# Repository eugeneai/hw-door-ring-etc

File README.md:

# hw-door-ring-etc
Door ring and clock with mp3 and calendar ic on the base of arduino uno

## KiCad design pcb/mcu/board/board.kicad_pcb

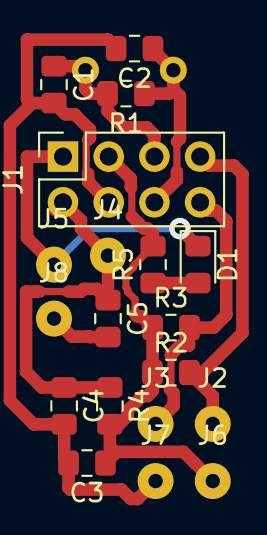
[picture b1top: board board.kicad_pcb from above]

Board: 2 copper layers, 20 parts (1 on the bottom side), 10 nets.

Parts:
C1, C2: 22p; C_0805_2012Metric_Pad1.15x1.40mm_HandSolder
C3, C4, C5: 100n; C_0805_2012Metric_Pad1.15x1.40mm_HandSolder
D1: LED; LED_0805_2012Metric_Pad1.15x1.40mm_HandSolder
J1: Conn_02x04_Odd_Even; PinSocket_2x04_P2.54mm_Vertical
J2: SCL; SolderWirePad_1x01_Drill0.8mm
J3: SDA; SolderWirePad_1x01_Drill0.8mm
J4: ~RST; SolderWirePad_1x01_Drill0.8mm
J5: PG4; SolderWirePad_1x01_Drill0.8mm
J6: VCC; SolderWirePad_1x01_Drill0.8mm
J7: GND; SolderWirePad_1x01_Drill0.8mm
J8: DTR; SolderWirePad_1x01_Drill0.8mm
R1: 1M; R_0805_2012Metric_Pad1.15x1.40mm_HandSolder
R2, R3: 10K; R_0805_2012Metric_Pad1.15x1.40mm_HandSolder
R4, R5: 1K; R_0805_2012Metric_Pad1.15x1.40mm_HandSolder
Y1: Crystal; Crystal_HC49-4H_Vertical

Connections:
GND: C1.2, C2.2, C3.2, C4.2, J1.4, J7.1
unnamed: C5.2, J8.1
unnamed: D1.2, R5.1
PG4: D1.1, J1.1, J5.1
SCL: J1.7, J2.1, R2.2
SDA: J1.8, J3.1, R3.2
VCC: C3.1, J1.3, J6.1, R2.1, R3.1, R4.2, R5.2
XTAL1: C2.1, J1.6, R1.1, Y1.2
XTAL2: C1.1, J1.5, R1.2, Y1.1
~RST: C4.1, C5.1, J1.2, J4.1, R4.1

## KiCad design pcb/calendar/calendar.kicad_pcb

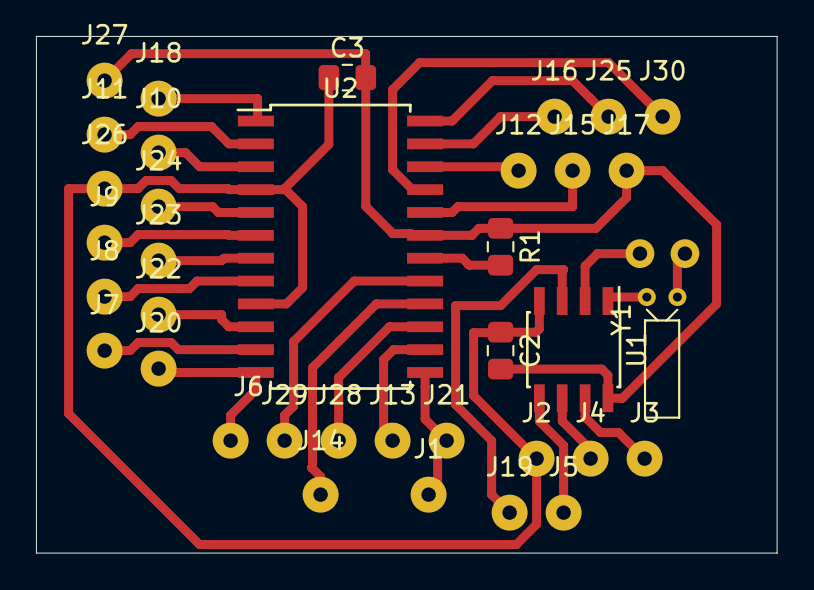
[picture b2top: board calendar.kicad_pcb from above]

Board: 4 copper layers, 41.1 x 28.7 mm, 37 parts (1 on the bottom side), 30 nets.

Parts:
C1: C; C_Disc_D3.0mm_W2.0mm_P2.50mm
C2, C3: 100n; C_0805_2012Metric_Pad1.15x1.40mm_HandSolder
J1, J2, J3, J4, J5, J6, J7, J8, J9, J10, J11, J12, J13, J14, J15, J16, J17, J18, J19, J20, J21, J22, J23, J24, J25, J26, J27, J28, J29, J30: J; SolderWirePad_1x01_Drill0.8mm
R1: 9K53; R_0805_2012Metric_Pad1.15x1.40mm_HandSolder
U1: PCF8563T; SOIC-8_3.9x4.9mm_P1.27mm
U2: MAX7219; SOIC-24W_7.5x15.4mm_P1.27mm
Y1: 32 768; Crystal_DS15_D1.5mm_L5.0mm_Horizontal

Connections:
+5V: C2.2, C3.2, J17.1, J27.1, R1.1, U1.8, U2.19
A: J13.1, U2.14
B: J14.1, U2.16
C: J15.1, U2.20
D: J16.1, U2.23
D0: J11.1, U2.2
D1: J7.1, U2.11
D2: J9.1, U2.6
D3: J23.1, U2.7
D4: J10.1, U2.3
D5: J22.1, U2.10
D6: J24.1, U2.5
D7: J8.1, U2.8
DIN: J18.1, U2.1
DOUT: J25.1, U2.24
DP: J12.1, U2.22
E: J30.1, U2.21
F: J28.1, U2.15
G: J29.1, U2.17
GND: C2.1, C3.1, J2.1, J26.1, U1.4, U2.4, U2.9
LOAD: J6.1, J20.1, U2.12
unnamed: C1.1, U1.2
unnamed: C1.2, Y1.2
unnamed: R1.2, U2.18
unnamed: U1.1, Y1.1
SCL: J4.1, U1.6
SCLK: J1.1, J21.1, U2.13
SDA: J5.1, U1.5
TCLK: J3.1, U1.7
T~INT: J19.1, U1.3

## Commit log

2019-04-06 Added code and doc
2019-04-06 Added ic docs.
2019-04-06 Added DFPlayer datasheet.
2019-04-07 Added some more ducs.
2019-04-07 Added PCB of clendar.
2019-04-09 Added 7-segment indicator theory.
2019-04-09 Show image in md.
2019-04-09 Another picture.
2019-04-09 Added new picture of pinout.
2019-04-16 Added more docs for mp3 player
2019-04-17 Moved pins around eliminating vias.
2019-04-18 New pcb
2019-04-18 Changed from pins to wire rings.
2019-04-20 Moved oints around
2019-04-20 Added driver for LCD7SEG*8
2019-04-21 Added ASCII Character set.
2019-04-22 Drive + as Celsius sign.
2019-04-23 Implementing pcf8563
2019-04-23 Added ATMega64A-16AU docs.
2019-04-23 Added XTAL provision of ATMega64A-16AU
2019-04-24 Renamed Atmel datasheet.
2019-04-25 Added showing time from RTC
2019-04-25 Ddded additional provision.
2019-04-26 Added DTR with a capacitor.
2019-04-28 New kicad tested.
2020-02-25 Added ATMega128 datasheet.
